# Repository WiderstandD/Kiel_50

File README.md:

# Kiel_50 - Programmable ESC for the BLDC and PMSM Motors
Kiel 50 is an Arduino UNO shield for driving sensor-less three-phase BLDC motor. The main advantage is the sinusoidal current drive. By monitoring the back-EMF (BEMF) the motor can run without the independent rotor position sensor aka hall sensor or encoder. The chip is able to sense the BEMF from very low rpm up to high rpm. The speed can be set and adjusted using PWM or SPI. The Kiel 50 shield comes with the main chip [A4964](https://www.allegromicro.com/en/Products/Motor-Drivers/BLDC-Drivers/A4964) from "Allegro MicroSystems". This chip is All-in-one: the motor controller, N-Channel MOSFET driver, voltage regulator, MCU watchdog. The ability to program this chip via SPI using Arduino makes it easy to use for many projects. After the configurations were uploaded to the controller and saved to the NVM it can run without Arduino as well.

Measurement of the three-phase (Voltage Ch.1,2,3)

Measurment of the three-phase (Voltage Ch.1,2,3 + Current Ch.4 (GN))

---

# Technical specification
|Characteristic|Symbol|Note|Raiting|Unit|
| --- | --- | --- | --- | --- |
|Supply voltage|Vsup| |5.5 - 50|V|
|Logic voltage|VLR|REG 25 - VLR|3.3 - 5|V|
|Maximal current|Imax|Fused: F2|10|A|
|Maximal logic current|Ilog|Fused: F1|290|mA|
|Gate drive regulator voltage|Vrg|REG 25 - VRG|8 or 11|V|
|Bridge PWM frequency|ƒpw|REG 0 - PW|14.2 - 50|Khz|
|PWM frequency (logic)|ƒpwm||500 - 1000|Hz|
|SPI frequency|ƒspi||2|Mhz|

# Safety features
|Feature|Description|
| --- | --- |
|Undervoltage lockout|Controller can detect the voltgae drop and switsch the motor off. Thus avoiding the risk of unpredictible behavior.|
|Peak current limit|Can be programmed using the MCU. Uses shunt for monitoring the current.|
|Ignition switch|The high-active input permitt the system start|
|Bridge MOSFET test|The controller can detect if the driving MOSFETs are broken or have any issues.|
|Windmill detection|If the motor rotetes, the controller can detect its speed and syncronise with it. Thus allowing further rotation without the braiking.|  
|MCU watchdog and reset||

# Driving modes
| Mode | Description |
| --- | --- |
| Closed-loop speed | Is used in many e-bike controllers. Acceleration, braking, reaction speed and others settings can be configured via SPI only. After the configuration was set, the speed input via SPI or PWM is acceptable. |
| Closed-loop current | The configuration is done via SPI only. The speed can be adjusted using SPI or PWM. | 
| Open-loop speed | The controller ignores the BEMF and keeps switchting the phases based ont the values of the ramp table. |

#### Hardware design features: 
1. Min component size 0802 SMD for easy hand soldering.
2. Radiator for the heat dissipation from the IC.
---

# How to start

### Hardware for the first start
- Kiel_50 board
- Three phase BLDC motor
- Arduino UNO
- Power supply 5.5V - 50V with at least 1A (for small motors)
- Main PC for programming

### Software for the first start
- Arduino IDE
- The Software for the Arduino UNO 

### Before start, test the board
1. First git clone the repository or download it to the main PC.
2. Navigate to the Kiel_50 folder.
3. Open /Kiel_50/Software/chip_test/chip_test_programm.ino file in Arduino IDE.
4. Select Arduoino UNO in the Borard manger and compile the chip_test_programm.ino.
5. By setting all switches on SW_DIP_x04(BLUE) to ON you enable the SPI communication with Arduino UNO.
6. Plug the Kiel 50 shield to Arduino UNO.
7. Flash Arduino UNO.
8. Connect the power supply to the board, avoid connectong the motor to the board.
9. Open the serial monitor, now you can monitor the supply voltage, chip temperatur, etc.
10. You can try to change the supply voltage (if it's possible). You have to see the voltage change in serial. 

### Frirst start
//ToDo 

---
# Keywords:
- ESC - electric speed controller
- BLDC - Brushless DC electric motor
- PMSM - Permanent magnet synchronous motor
- DC - Direct current
- IDE - Integrated Development Environment
---

# Notes:
#### Aplication example: 
1. Free rotating motors
2. Pump 
3. Fans and blowers

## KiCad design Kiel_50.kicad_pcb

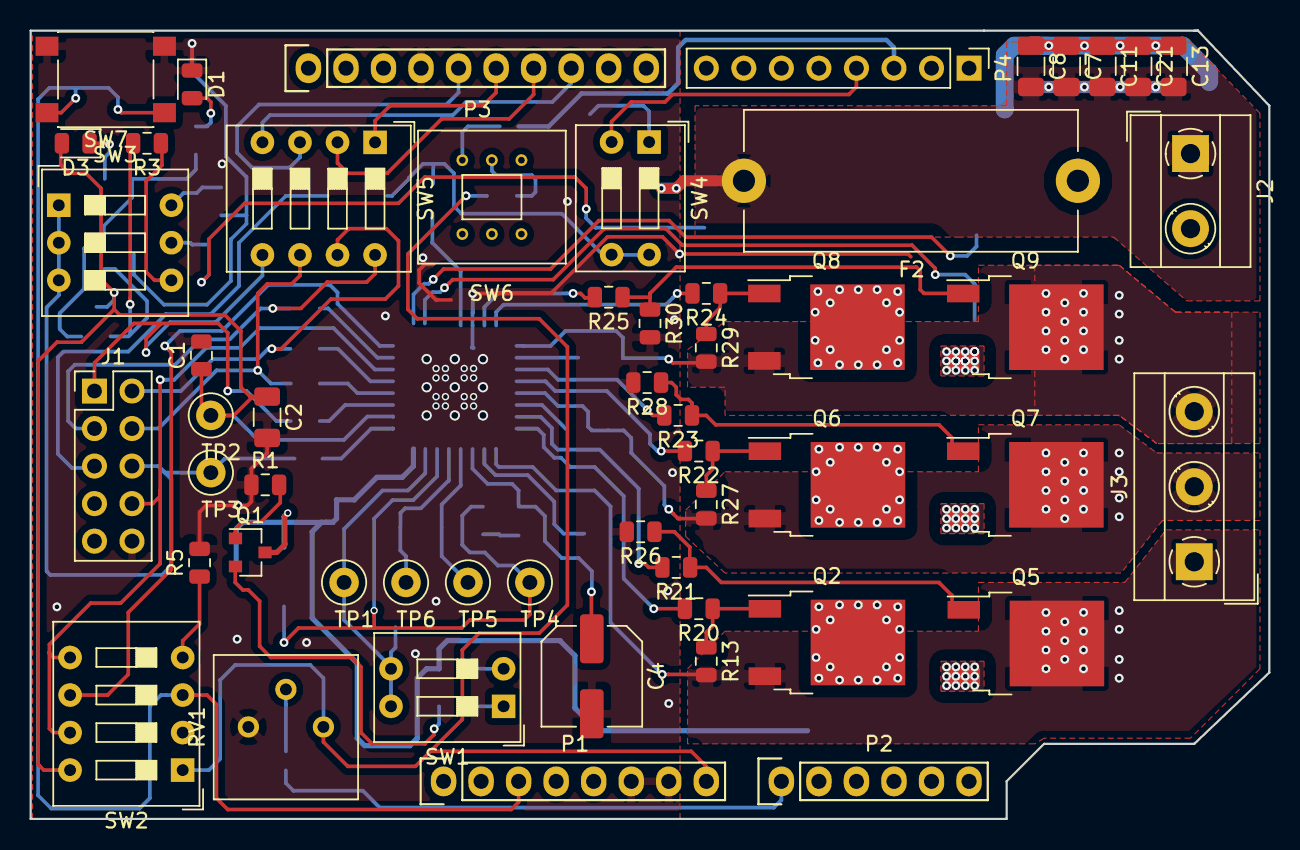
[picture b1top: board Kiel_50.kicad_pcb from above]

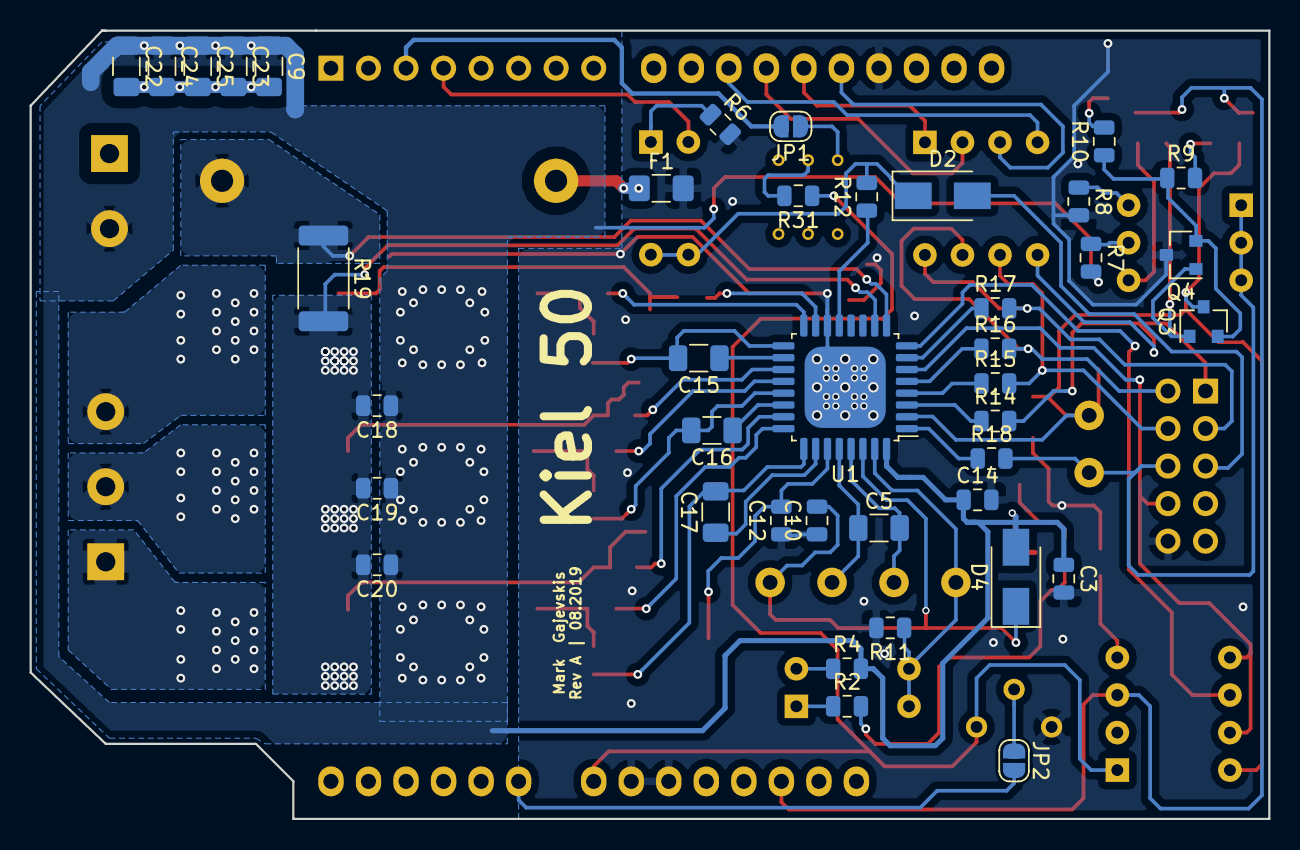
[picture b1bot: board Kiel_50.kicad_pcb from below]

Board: 2 copper layers, 83.8 x 53.3 mm, 94 parts (40 on the bottom side), 69 nets.

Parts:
C1, C10, C12, C14, C18, C19, C20: 100nF; C_0805_2012Metric
C2, C7, C8, C9, C11, C13, C21, C22, C23, C24, C25: 1µF; C_1206_3216Metric
C3: 10nF; C_0805_2012Metric
C4: 100µF; C_Elec_6.3x7.7
C5, C15, C16, C17: 470nF; C_1206_3216Metric
D1: LED(GRN); LED_0805_2012Metric
D2, D4: D_Schottky(SS210); D_SMA
D3: LED(RED); LED_0805_2012Metric
F1: Fuse_SMD_290mA; Fuse_1206_3216Metric_Pad1.42x1.75mm_HandSolder
F2: Fuse_10A; Fuseholder_Cylinder-5x20mm_Stelvio-Kontek_PTF78_Horizontal_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
J1: Conn_02x05_Odd_Even; PinHeader_2x05_P2.54mm_Vertical
J2: Screw_Terminal_01x04_Vin(P=5.08mm); TerminalBlock_MetzConnect_Type101_RT01602HBWC_1x02_P5.08mm_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
J3: Screw_Terminal_01x03_Motor(P=5.08mm); TerminalBlock_MetzConnect_Type101_RT01603HBWC_1x03_P5.08mm_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
JP1, JP2: SolderJumper_2_Open; SolderJumper-2_P1.3mm_Open_RoundedPad1.0x1.5mm
P1: Power; Socket_Strip_Arduino_1x08
P2: Analog; Socket_Strip_Arduino_1x06
P3: Digital; Socket_Strip_Arduino_1x10
P4: Digital; PinHeader_1x08_P2.54mm_Vertical
Q1, Q4: BC807; SOT-23
Q2, Q5, Q6, Q7, Q8, Q9: RU7570L; TO-252-2
Q3: BC847; SOT-23
R1, R5, R6, R11: 10K; R_0805_2012Metric
R2, R3, R4, R7, R8, R31: 1K; R_0805_2012Metric
R9, R10: 430R; R_0805_2012Metric
R12, R18, R20, R21, R22, R23, R24, R25: 100R; R_0805_2012Metric
R13, R26, R27, R28, R29, R30: 100K; R_0805_2012Metric
R14, R15, R16, R17: 240R; R_0805_2012Metric
R19: 0.02R; R_2512_6332Metric
RV1: R_POT(Package: 3386P); Potentiometer_Bourns_3386P_Vertical
SW1: SW_DIP_x02(RED); SW_DIP_SPSTx02_Slide_9.78x7.26mm_W7.62mm_P2.54mm
SW2, SW5: SW_DIP_x04(BLUE); SW_DIP_SPSTx04_Slide_9.78x12.34mm_W7.62mm_P2.54mm
SW3: SW_DIP_x03(RED); SW_DIP_SPSTx03_Slide_9.78x9.8mm_W7.62mm_P2.54mm
SW4: SW_DIP_x02(BLUE); SW_DIP_SPSTx02_Slide_9.78x7.26mm_W7.62mm_P2.54mm
SW6: User_pusch_button; XKB7070-Z-92
SW7: SW_Push; SW_Push_1P1T_NO_6x6mm_H9.5mm
TP1: Keystone 5014; TestPoint_Loop_D2.50mm_Drill1.0mm
TP2, TP3, TP4, TP5, TP6: Keystone 5001; TestPoint_Loop_D2.50mm_Drill1.0mm
U1: A4964; LQFP-32_7x7mm_P0.8mm_with_heat_pad

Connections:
A_Phase: C17.2, J3.1, Q2.3, Q5.2, R13.2, U1.25
B_Phase: C16.2, J3.2, Q6.3, Q7.2, R27.2, U1.21
CSM: F2.1, R19.1, U1.9
CSP: C18.2, C19.2, C20.2, Q5.3, Q7.3, Q9.3, R19.2, U1.10
C_Phase: C15.2, J3.3, Q8.3, Q9.2, R29.2, U1.17
GHA: R20.2, U1.24
GHB: R22.2, U1.20
GHC: R24.2, U1.16
GLA: R21.2, U1.23
GLB: R23.2, U1.19
GLC: R25.2, U1.15
GND: C1.2, C2.2, C3.2, C4.2, C10.1, C12.1, C14.2, D1.1, F1.2, J1.10, P1.6, P1.7, P3.4, Q4.3, R1.1, R5.2, R6.2, R8.2, R11.2, R26.2, R28.2, R30.2, RV1.3, SW7.2, U1.14, U1.33
GNDPWR: C7.2, C8.2, C9.2, C11.2, C13.2, C21.2, C22.2, C23.2, C24.2, C25.2, F1.1, F2.2, J2.1
MCU_Analog_Pot: JP2.2, P2.1
MCU_IG: Q1.1, R1.2
MCU_MISO: P3.6, SW5.1
MCU_MOSI: P3.7, SW5.2
MCU_PWM: P4.4, SW4.2
MCU_Push_button: JP1.2, P4.3
MCU_RST: P1.3, SW2.3, SW7.1
MCU_SCK: P3.5, SW5.3
MCU_STRn: P3.8, SW5.4
MCU_Vin: P1.8, R31.1, RV1.1, SW2.1
unnamed: C1.1, C2.1, D3.2, Q3.3, SW2.8, TP2.1, U1.2
unnamed: C5.1, TP5.1, U1.28
unnamed: C5.2, TP6.1, U1.29
unnamed: C10.2, D4.1, TP4.1, U1.30
unnamed: C4.1, C12.2, U1.27
unnamed: C15.1, U1.18
unnamed: C16.1, U1.22
unnamed: C17.1, U1.26
unnamed: D1.2, R10.2
unnamed: D2.1, R12.2, SW4.3, SW4.4
unnamed: D2.2, J1.5
unnamed: D3.1, R9.2
unnamed: J1.1, R14.2, SW5.5
unnamed: J1.2, R16.2, SW5.7
unnamed: J1.3, R17.2, SW5.8
unnamed: J1.4, R15.2, SW5.6
unnamed: J1.6, R18.2, SW3.1, SW3.2, SW3.3, TP3.1
unnamed: J1.8, SW2.5, SW2.7, U1.6
unnamed: JP1.1, SW6.1
unnamed: JP2.1, RV1.2
unnamed: Q1.2, R2.2
unnamed: Q2.1, R13.1, R20.1
unnamed: Q3.1, Q4.1, R3.2
unnamed: Q3.2, Q4.2, R9.1, R10.1
unnamed: Q5.1, R21.1, R26.1
unnamed: Q6.1, R22.1, R27.1
unnamed: Q7.1, R23.1, R28.1
unnamed: Q8.1, R24.1, R29.1
unnamed: Q9.1, R25.1, R30.1
unnamed: R2.1, SW1.1
unnamed: R3.1, SW3.4
unnamed: R4.1, SW1.2
unnamed: R5.1, SW2.4
unnamed: R6.1, SW4.1
unnamed: R7.1, SW3.5
unnamed: R8.1, SW3.6
unnamed: R11.1, SW1.3, SW1.4, TP1.1, U1.31
unnamed: R12.1, U1.13
unnamed: R14.1, U1.3
unnamed: R15.1, U1.4
unnamed: R16.1, U1.5
unnamed: R17.1, U1.7
unnamed: R18.1, U1.1
unnamed: R31.2, SW6.2
unnamed: SW2.6, U1.8
VDD: C3.1, C7.1, C8.1, C9.1, C11.1, C13.1, C14.1, C18.1, C19.1, C20.1, C21.1, C22.1, C23.1, C24.1, C25.1, D4.2, J2.2, Q1.3, Q2.2, Q6.2, Q8.2, R4.2, R7.2, U1.32

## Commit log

2019-08-28 commant
2019-08-28 oscillograms
2019-11-22 Software added.
    Chip test programm and motor controll programm added
2019-11-22 Update Kiel_50_Hbottom.jpg
    Croped the Kiel_50_Hbottom.jpg
2019-12-06 Software revised
2019-12-06 Minor changes in software pack.
2020-04-22 minor changes
    Added ploted schematic, fixed errors.
